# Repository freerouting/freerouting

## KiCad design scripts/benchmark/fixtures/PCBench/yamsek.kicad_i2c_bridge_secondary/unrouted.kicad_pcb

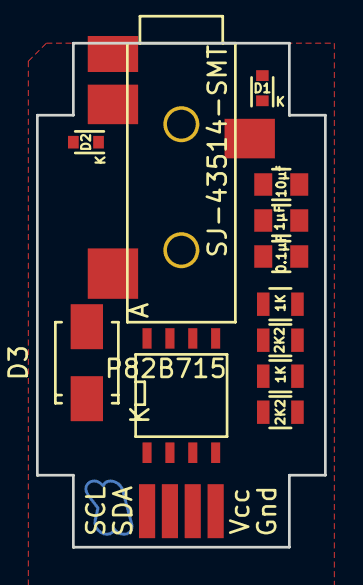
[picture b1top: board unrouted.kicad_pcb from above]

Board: 2 copper layers, 16.0 x 28.0 mm, 14 parts (1 on the bottom side), 7 nets, no tracks yet.

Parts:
C1: 10µf; C_0805
C2: 1µF; C_0805
C3: 0.1µF; C_0805
D1, D2: VESD05a1; SOD-523
D3: SS14; SMA_Standard
I2C1: CONN_01X04; solderPads_4_Grove_I2C
R1, R2: 1K; R_0805
R3, R4: 2K2; R_0805
TRRS1: SJ-43514-SMT; audio_smd_SJ-43514-SMT
U1: P82B715; SOIC-8-N
svg2mod: G***; logo

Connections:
+5V: C1.1, C2.1, C3.1, D3.1, I2C1.3, R1.2, R2.2, R3.2, R4.2, U1.8
/i2c_bridge_common/SCL_connector: D1.1, R1.1, TRRS1.3, U1.7
/i2c_bridge_common/SCL_inside: I2C1.1, R3.1, U1.6
/i2c_bridge_common/SDA_connector: D2.1, R2.1, TRRS1.4, U1.2
/i2c_bridge_common/SDA_inside: I2C1.2, R4.1, U1.3
GND: C1.2, C2.2, C3.2, D1.2, D2.2, I2C1.4, TRRS1.1, U1.4
unnamed: D3.2, TRRS1.2

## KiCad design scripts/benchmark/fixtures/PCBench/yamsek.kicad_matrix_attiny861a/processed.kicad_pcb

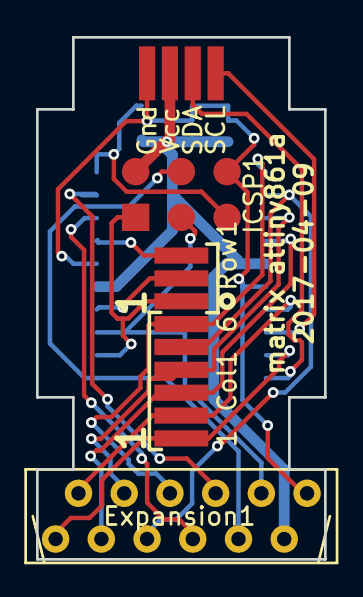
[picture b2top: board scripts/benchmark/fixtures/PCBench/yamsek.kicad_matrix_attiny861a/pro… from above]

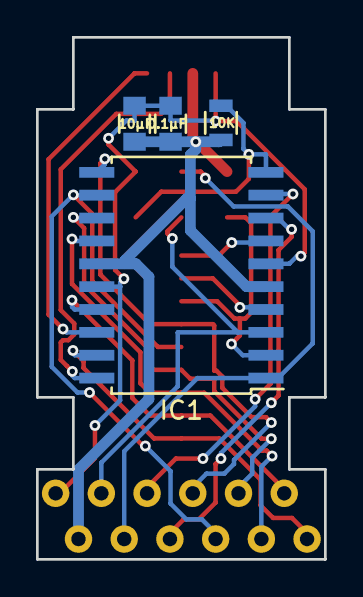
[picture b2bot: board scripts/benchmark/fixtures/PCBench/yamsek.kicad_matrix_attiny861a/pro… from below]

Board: 2 copper layers, 16.0 x 29.0 mm, 9 parts (4 on the bottom side), 18 nets.

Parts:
C1: 10µF; C_0805
C2: 0.1µF; C_0805
Col1: CONN_01X06; solderPads_6
Expansion1: CONN_01X12; microMatch-12_90_THT
I2C1: CONN_01X04; solderPads_4_Grove_I2C
IC1: ATTINY861A-S; SOIC-20W_7.5x12.8mm_Pitch1.27mm
ICSP1: CONN_02X03; ICSP_BIG_pads
R1: 10K; R_0805
Row1: CONN_01X03; solderPads_3

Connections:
+5V: C1.1, C2.1, Expansion1.11, I2C1.3, IC1.5, IC1.15, ICSP1.2, R1.2
/ADC_H+int0: Expansion1.8, IC1.9
/ADC_V: Expansion1.7, IC1.8
/MiSo: IC1.2, ICSP1.1, Row1.1
/MoSi: Expansion1.9, IC1.1, ICSP1.4
/Rst: IC1.10, ICSP1.5, R1.1
/SCL: I2C1.1, IC1.18
/SCL_2: Expansion1.10, IC1.3, ICSP1.3
/SDA: I2C1.2, IC1.20
GND: C1.2, C2.2, Expansion1.12, I2C1.4, IC1.6, IC1.16, ICSP1.6
unnamed: Col1.1, Expansion1.1, IC1.19
unnamed: Col1.2, Expansion1.2, IC1.17
unnamed: Col1.3, Expansion1.3, IC1.14
unnamed: Col1.4, Expansion1.4, IC1.13
unnamed: Col1.5, Expansion1.5, IC1.12
unnamed: Col1.6, Expansion1.6, IC1.11
unnamed: IC1.4, Row1.2
unnamed: IC1.7, Row1.3

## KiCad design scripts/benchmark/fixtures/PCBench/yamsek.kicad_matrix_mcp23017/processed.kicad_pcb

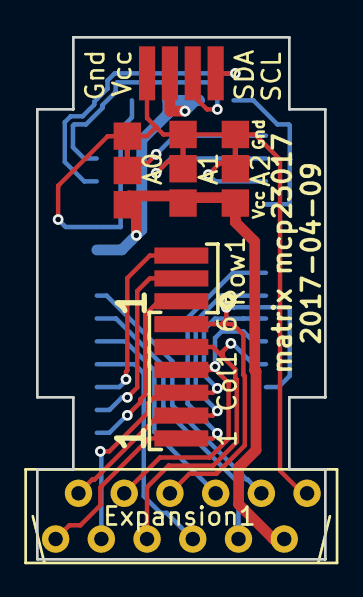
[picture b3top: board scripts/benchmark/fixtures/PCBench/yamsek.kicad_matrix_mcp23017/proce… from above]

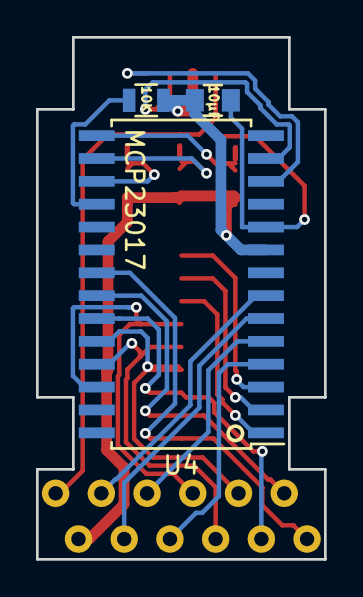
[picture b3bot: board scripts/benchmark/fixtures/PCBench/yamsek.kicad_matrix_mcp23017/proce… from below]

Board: 2 copper layers, 16.0 x 29.0 mm, 10 parts (3 on the bottom side), 21 nets.

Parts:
A0, A1, A2: address_sel; addr_jumper
C1: 10µF; C_0805
Col1: CONN_01X06; solderPads_6
Expansion1: CONN_01X12; microMatch-12_90_THT
I2C1: CONN_01X04; solderPads_4_Grove_I2C
R1: 10K; R_0805
Row1: CONN_01X03; solderPads_3
U4: MCP23017; SOIC-28W_7.5x17.9mm_Pitch1.27mm

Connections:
+5V: A0.1, A1.1, A2.1, C1.1, Expansion1.11, I2C1.3, R1.2, U4.9
/SCL: I2C1.1, U4.12
/SDA: I2C1.2, U4.13
GND: A0.3, A1.3, A2.3, C1.2, Expansion1.12, I2C1.4, U4.10
unnamed: A0.2, U4.15
unnamed: A1.2, U4.16
unnamed: A2.2, U4.17
unnamed: Col1.1, Expansion1.1, U4.21
unnamed: Col1.2, Expansion1.2, U4.22
unnamed: Col1.3, Expansion1.3, U4.23
unnamed: Col1.4, Expansion1.4, U4.24
unnamed: Col1.5, Expansion1.5, U4.25
unnamed: Col1.6, Expansion1.6, U4.26
unnamed: Expansion1.7, U4.4
unnamed: Expansion1.8, U4.5
unnamed: Expansion1.9, U4.6
unnamed: Expansion1.10, U4.7
unnamed: R1.1, U4.18
unnamed: Row1.1, U4.1
unnamed: Row1.2, U4.2
unnamed: Row1.3, U4.3

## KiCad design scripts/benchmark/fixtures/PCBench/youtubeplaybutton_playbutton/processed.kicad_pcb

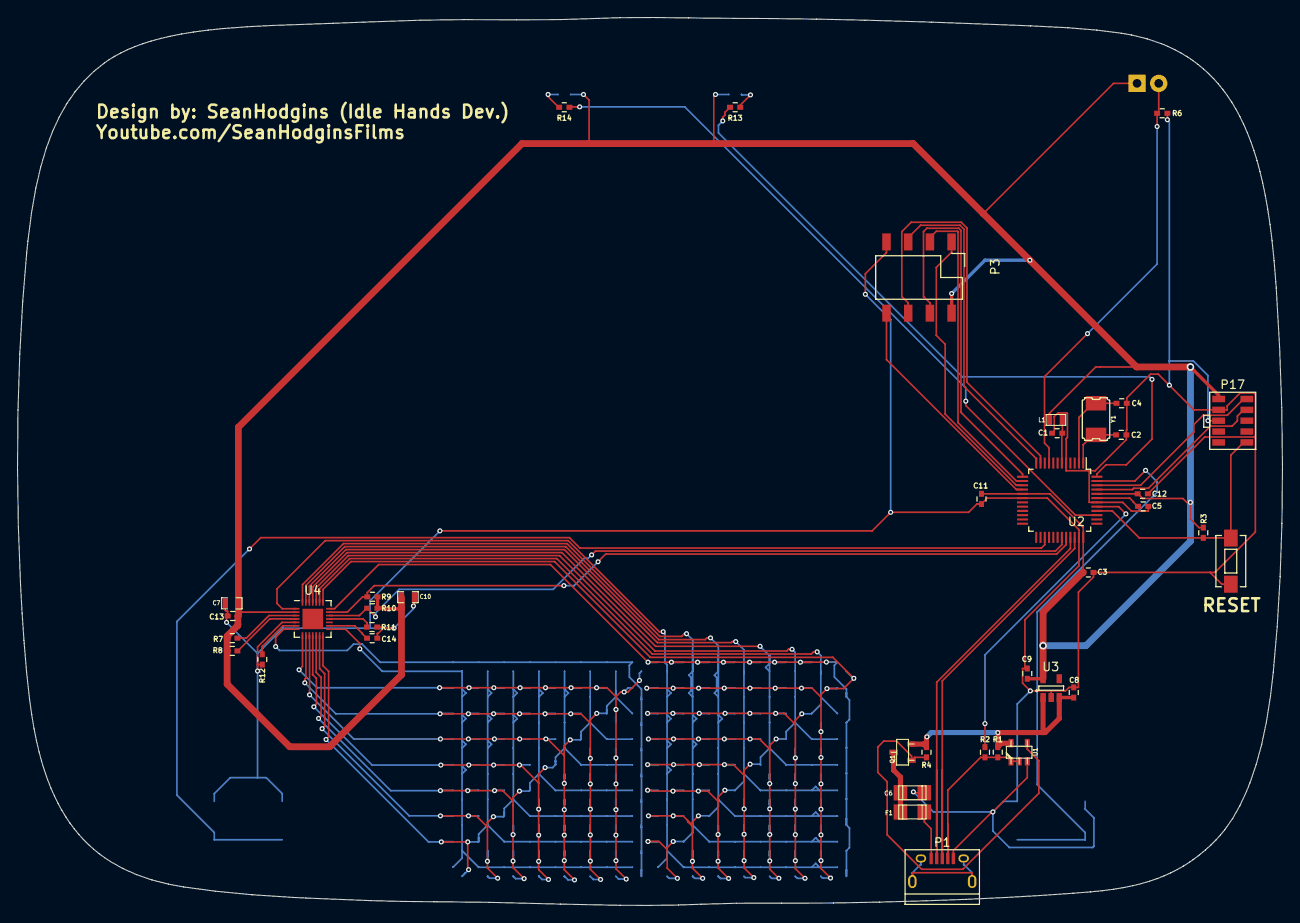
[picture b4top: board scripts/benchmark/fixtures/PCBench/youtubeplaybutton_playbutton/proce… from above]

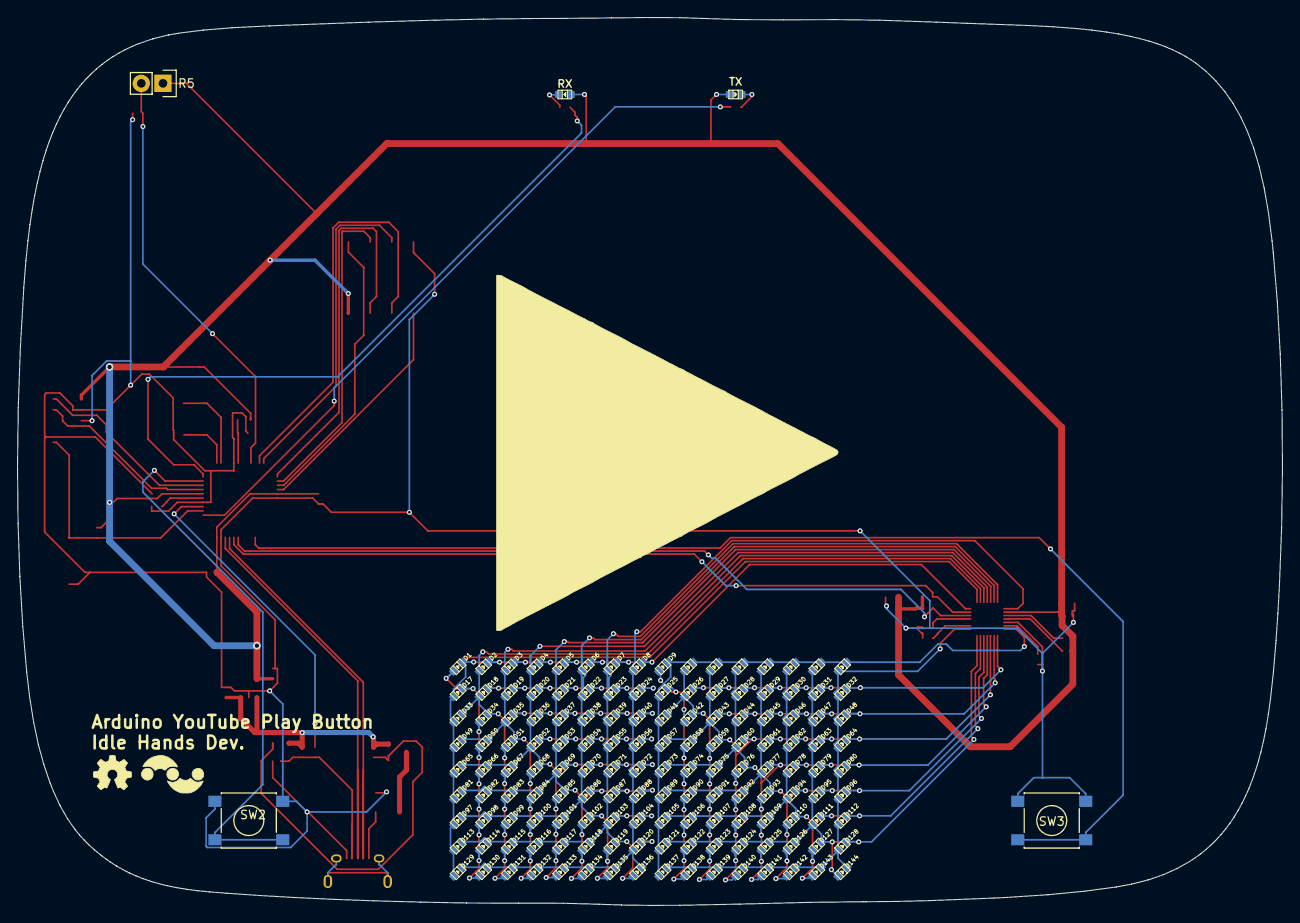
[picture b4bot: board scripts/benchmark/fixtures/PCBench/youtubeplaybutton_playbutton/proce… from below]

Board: 2 copper layers, 148.1 x 103.9 mm, 188 parts (149 on the bottom side), 55 nets.

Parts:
C1, C3, C5, C11, C12, C13, C14: 0.1uF; C_0402_Hand
C2, C4: 15pF; C_0402_Hand
C6: 2.2uF; c_1206
C7, C10: 10uF; C_SM0603
C8: 1uF; C_0402_Hand
C9: 2.2uF; C_0402_Hand
D1, D2, D3, D4, D5, D6, D7, D8, D9, D10, D11, D12, D13, D14, D15, D16, D17, D18, D19, D20, D21, D22, D23, D24, D25, D26, D27, D28, D29, D30, D31, D32, D33, D34, D35, D36, D37, D38, D39, D40, D41, D42, D43, D44, D45, D46, D47, D48, D49, D50, D51, D52, D53, D54, D55, D56, D57, D58, D59, D60, D61, D62, D63, D64, D65, D66, D67, D68, D69, D70, D71, D72, D73, D74, D75, D76, D77, D78, D79, D80, D81, D82, D83, D84, D85, D86, D87, D88, D89, D90, D91, D92, D93, D94, D95, D96, D97, D98, D99, D100, D101, D102, D103, D104, D105, D106, D107, D108, D109, D110, D111, D112, D113, D114, D115, D116, D117, D118, D119, D120, D121, D122, D123, D124, D125, D126, D127, D128, D129, D130, D131, D132, D133, D134, D135, D136, D137, D138, D139, D140, D141, D142, D143, D144: LED; Led_0603
D1006: RX; Led_0603
D1007: TX; Led_0603
F1: 500mA; c_1206
L1: FB - 30Ohm; R_SM0603
P1: USB_OTG; USB_Micro-B
P3: ESP8266; Pin_Header_SMD_2x04
P17: DBG_CONN; Pin_Header_SMD_2x05_Pitch1.27mm
Q1: Q_PMOS_GSD; SOT23
R1: 100k; R_0402_Hand
R2: 330; R_0402_Hand
R3, R6: 10k; R_0402_Hand
R4: 47K; R_0402_Hand
R5: Photores; Pin_Header_Straight_1x02
R7, R8, R9, R10, R11, R12: 20k; R_0402_Hand
R13, R14: 1k; R_0402_Hand
SW2, SW3: SW_PUSH; SW_SPST_PTS645
SW4: SW_PUSH; SW_SPST_EVQPE1
U1: 74AHC1G125; sot23-5
U2: SAMD21G18; TQFP-48_7x7mm_Pitch0.5mm
U3: AP2112K-3.3V; SOT-23-5
U4: IS31FL3731; QFN-28-1EP_4x4mm_Pitch0.4mm
Y1: Crystal_Small; crystal_smd_5x3.2mm

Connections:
+3V3: C3.1, C7.1, C9.1, C10.1, C11.1, C12.1, C13.1, D1006.2, D1007.2, L1.1, P3.2, P17.1, R3.1, R5.1, R7.2, R8.2, R9.2, R10.2, U2.17, U2.36, U2.44, U3.5, U4.2
/BUT1: SW2.1, U2.47
/BUT2: SW3.1, U2.27
/CA1: D1.1, D2.1, D3.1, D4.1, D5.1, D6.1, D7.1, D8.1, D17.2, D33.2, D49.2, D65.2, D81.2, D97.2, D113.2, D129.2, U4.21
/CA2: D1.2, D17.1, D18.1, D19.1, D20.1, D21.1, D22.1, D23.1, D24.1, D34.2, D50.2, D66.2, D82.2, D98.2, D114.2, D130.2, U4.22
/CA3: D2.2, D18.2, D33.1, D34.1, D35.1, D36.1, D37.1, D38.1, D39.1, D40.1, D51.2, D67.2, D83.2, D99.2, D115.2, D131.2, U4.23
/CA4: D3.2, D19.2, D35.2, D49.1, D50.1, D51.1, D52.1, D53.1, D54.1, D55.1, D56.1, D68.2, D84.2, D100.2, D116.2, D132.2, U4.24
/CA5: D4.2, D20.2, D36.2, D52.2, D65.1, D66.1, D67.1, D68.1, D69.1, D70.1, D71.1, D72.1, D85.2, D101.2, D117.2, D133.2, U4.25
/CA6: D5.2, D21.2, D37.2, D53.2, D69.2, D81.1, D82.1, D83.1, D84.1, D85.1, D86.1, D87.1, D88.1, D102.2, D118.2, D134.2, U4.26
/CA7: D6.2, D22.2, D38.2, D54.2, D70.2, D86.2, D97.1, D98.1, D99.1, D100.1, D101.1, D102.1, D103.1, D104.1, D119.2, D135.2, U4.27
/CA8: D7.2, D23.2, D39.2, D55.2, D71.2, D87.2, D103.2, D113.1, D114.1, D115.1, D116.1, D117.1, D118.1, D119.1, D120.1, D136.2, U4.28
/CA9: D8.2, D24.2, D40.2, D56.2, D72.2, D88.2, D104.2, D120.2, D129.1, D130.1, D131.1, D132.1, D133.1, D134.1, D135.1, D136.1, U4.1
/CB1: D9.1, D10.1, D11.1, D12.1, D13.1, D14.1, D15.1, D16.1, D25.2, D41.2, D57.2, D73.2, D89.2, D105.2, D121.2, D137.2, U4.7
/CB2: D9.2, D25.1, D26.1, D27.1, D28.1, D29.1, D30.1, D31.1, D32.1, D42.2, D58.2, D74.2, D90.2, D106.2, D122.2, D138.2, U4.8
/CB3: D10.2, D26.2, D41.1, D42.1, D43.1, D44.1, D45.1, D46.1, D47.1, D48.1, D59.2, D75.2, D91.2, D107.2, D123.2, D139.2, U4.9
/CB4: D11.2, D27.2, D43.2, D57.1, D58.1, D59.1, D60.1, D61.1, D62.1, D63.1, D64.1, D76.2, D92.2, D108.2, D124.2, D140.2, U4.10
/CB5: D12.2, D28.2, D44.2, D60.2, D73.1, D74.1, D75.1, D76.1, D77.1, D78.1, D79.1, D80.1, D93.2, D109.2, D125.2, D141.2, U4.11
/CB6: D13.2, D29.2, D45.2, D61.2, D77.2, D89.1, D90.1, D91.1, D92.1, D93.1, D94.1, D95.1, D96.1, D110.2, D126.2, D142.2, U4.12
/CB7: D14.2, D30.2, D46.2, D62.2, D78.2, D94.2, D105.1, D106.1, D107.1, D108.1, D109.1, D110.1, D111.1, D112.1, D127.2, D143.2, U4.13
/CB8: D15.2, D31.2, D47.2, D63.2, D79.2, D95.2, D111.2, D121.1, D122.1, D123.1, D124.1, D125.1, D126.1, D127.1, D128.1, D144.2, U4.14
/CB9: D16.2, D32.2, D48.2, D64.2, D80.2, D96.2, D112.2, D128.2, D137.1, D138.1, D139.1, D140.1, D141.1, D142.1, D143.1, D144.1, U4.15
/CH_PD: P3.5, U2.12
/GPIO0: P3.3, U2.14
/GPIO2: P3.6, U2.11
/PHOTO: R5.2, R6.1, U2.9
/RESET_ESP: P3.4, U2.13
/RXI: P3.8, U2.16
/RXLED: R13.1, U2.48
/TXLED: R14.1, U2.39
/TXO: P3.1, U2.15
GND: C1.2, C2.2, C3.2, C4.2, C5.2, C6.2, C7.2, C8.2, C9.2, C10.2, C11.2, C12.2, C13.2, C14.2, P1.5, P3.7, P17.3, P17.5, R6.2, R11.2, R12.1, SW2.2, SW3.2, SW4.2, U1.3, U2.5, U2.18, U2.35, U2.42, U3.2, U4.5
unnamed: C1.1, L1.2, U2.6
unnamed: C2.1, U2.1, Y1.2
unnamed: C4.1, U2.2, Y1.1
unnamed: C5.1, U2.43
unnamed: C14.1, U4.16
unnamed: D1006.1, R13.2
unnamed: D1007.1, R14.2
unnamed: F1.1, P1.1
unnamed: Q1.1, R4.2, U1.4
unnamed: R7.1, U4.3
unnamed: R8.1, U4.4
unnamed: R11.1, U4.18
unnamed: R12.2, U4.6
RESET: P17.10, R3.2, SW4.1, U2.40
SCL: R9.1, U2.32, U4.20
SDA: R10.1, U2.31, U4.19
SWCLK: P17.4, U2.45
SWDIO: P17.2, U2.46
USB_D+: P1.3, U2.34
USB_D-: P1.2, U2.33
USB_HOST_EN: R2.2, U2.41
USB_ID: P1.4, R1.2, R2.1, U1.1, U1.2
VCC: C8.1, Q1.2, R1.1, R4.1, U1.5, U3.1, U3.3
VCOM: C6.1, F1.2, Q1.3
